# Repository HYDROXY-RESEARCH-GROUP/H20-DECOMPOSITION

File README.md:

# H20-DECOMPOSITION
H20 to HHO Genertor

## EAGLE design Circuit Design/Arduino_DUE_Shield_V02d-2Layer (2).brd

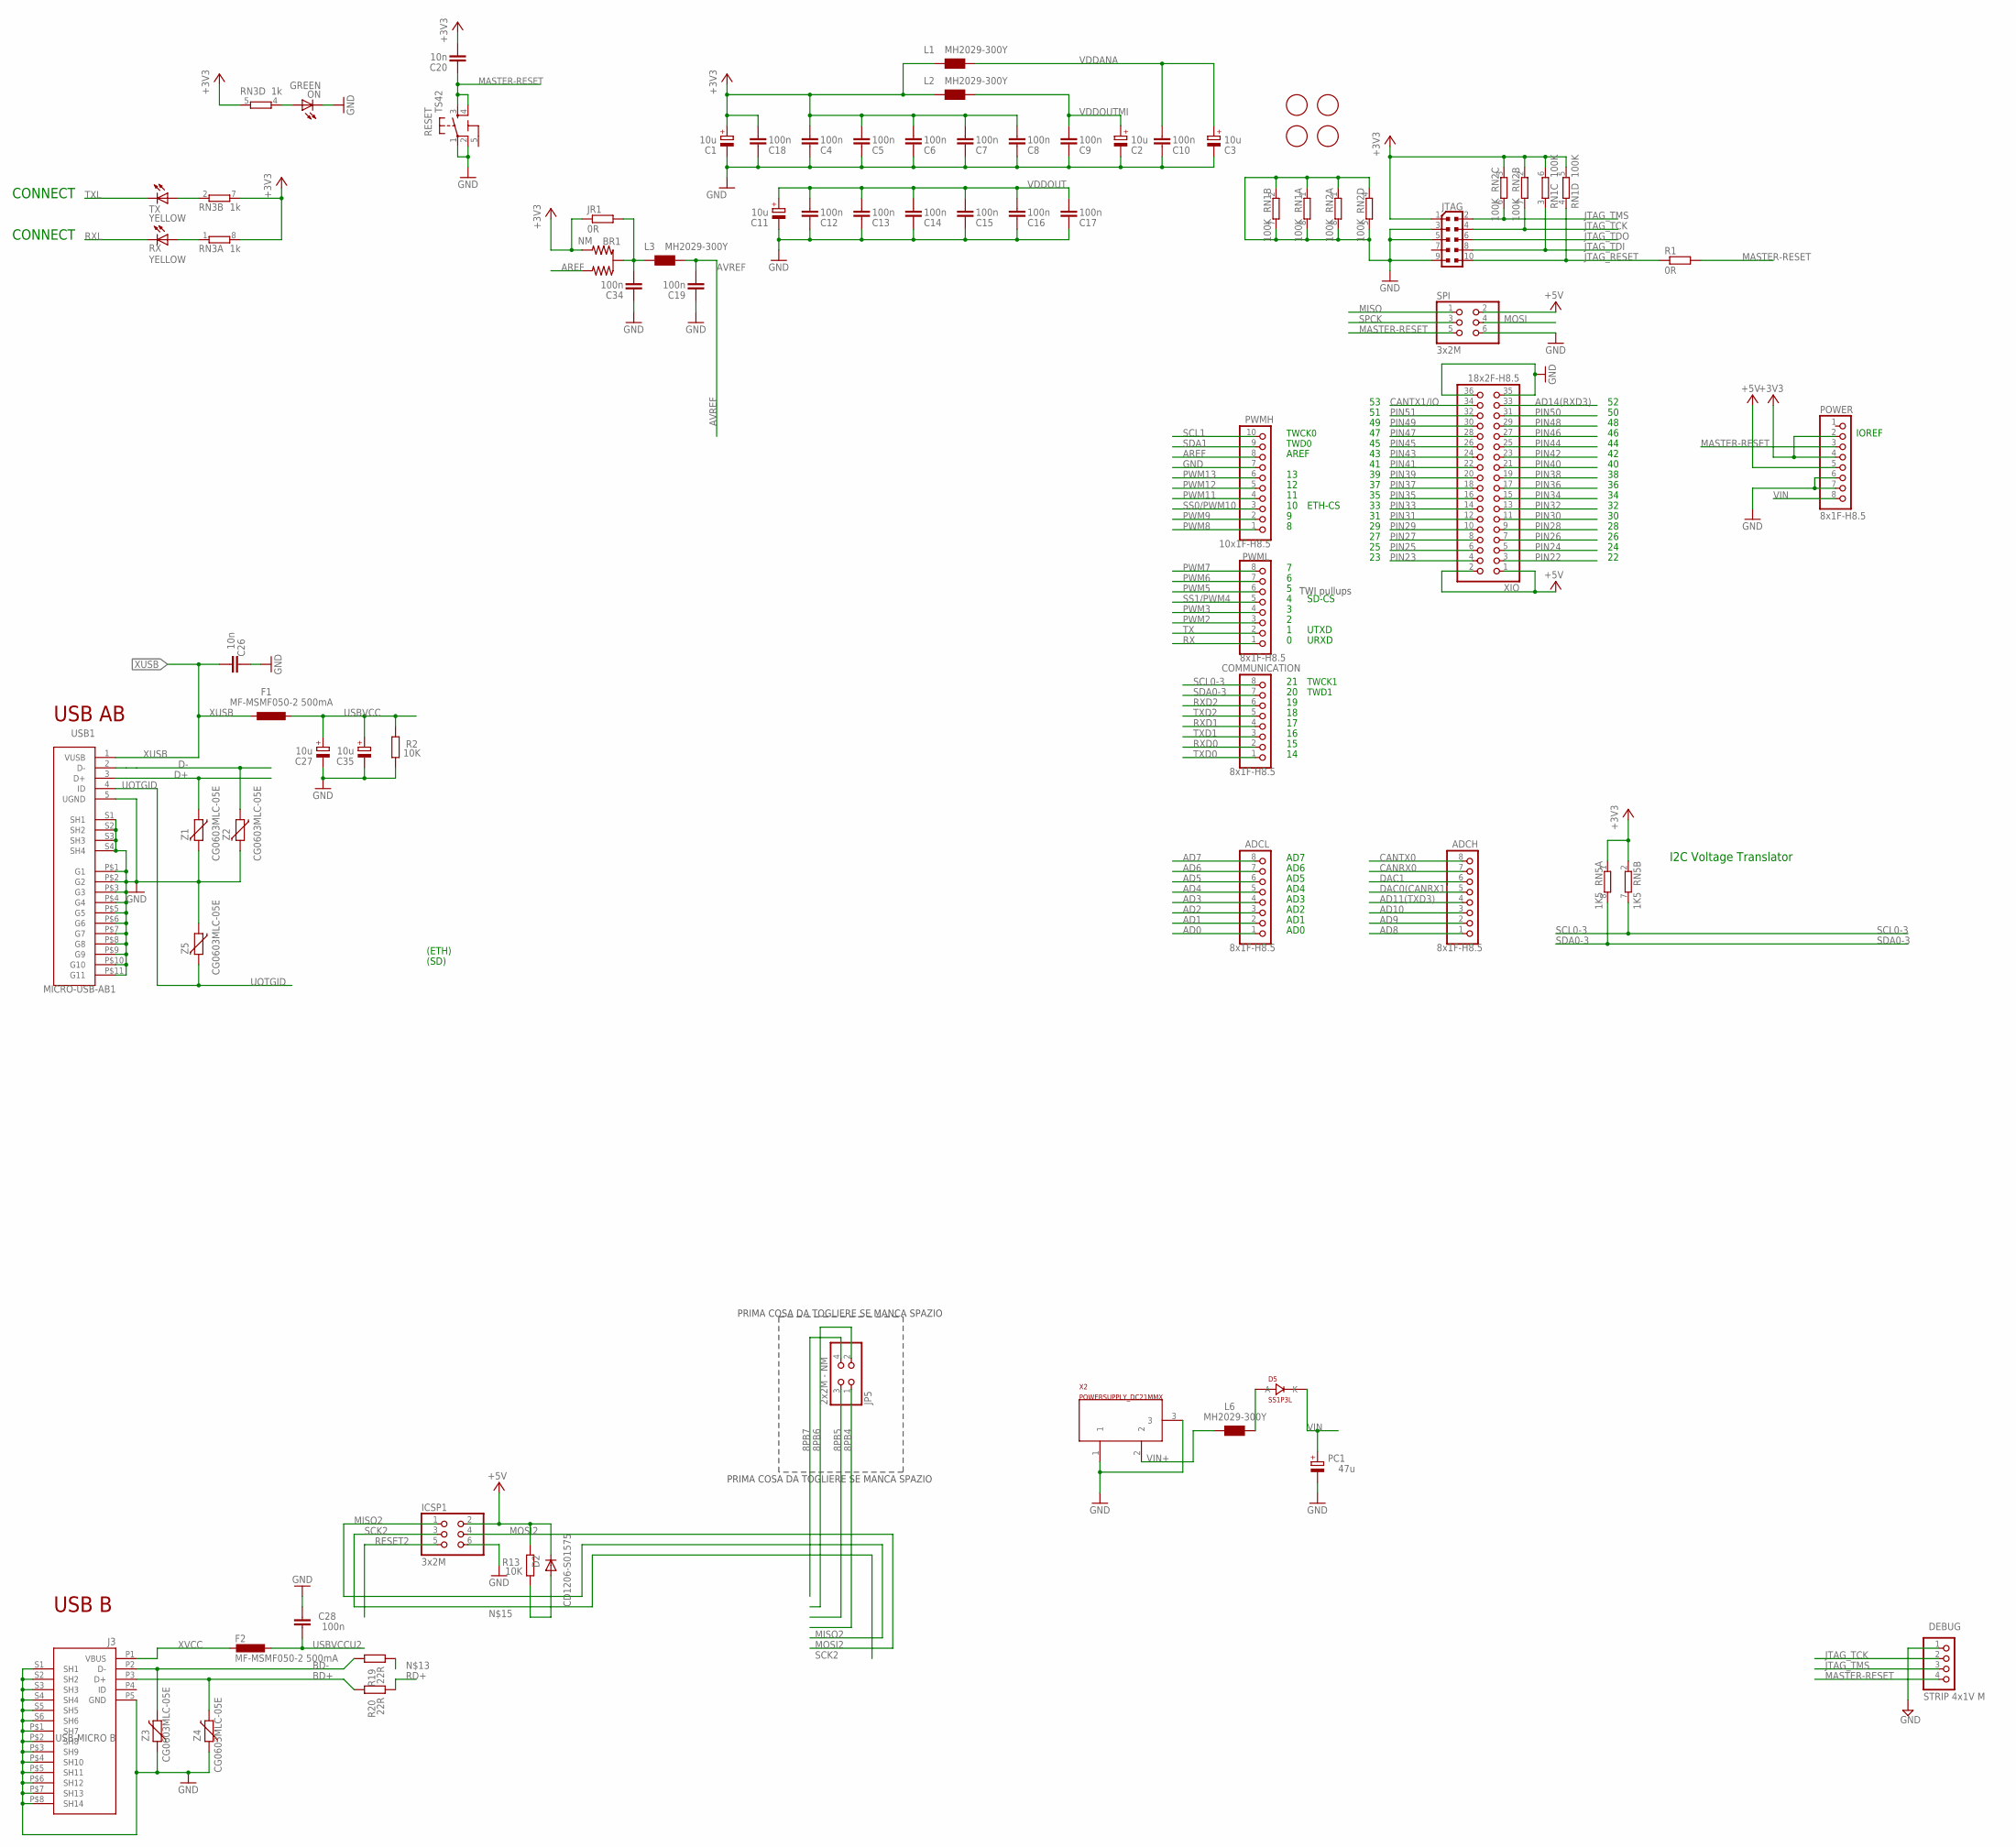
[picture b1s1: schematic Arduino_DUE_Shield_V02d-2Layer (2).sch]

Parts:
ADCH: 8x1F-H8.5; 1X08
ADCL: 8x1F-H8.5; 1X08
BR1: NM; J0402
C1, C2, C3, C11, C27, C35: 10u; SMC_B
C4, C5, C6, C7, C8, C9, C10, C12, C13, C14, C15, C16, C17, C18, C19, C28, C34: 100n; C0402
C20, C26: 10n; C0402
COMMUNICATION: 8x1F-H8.5; 1X08
D2: CD1206-S01575; MINIMELF
D5: SS1P3L; DO220AAL
DEBUG: STRIP 4x1V M; 1X04
F1, F2: MF-MSMF050-2 500mA; L1812
FID1, FID2, FID3, FID4: FIDUCIALMOUNT; FIDUCIA-MOUNT
ICSP1: 3x2M; 2X03
J3: USB-MICRO B; CON2_USB_MICRO_B_AT
JP5: 2x2M - NM; 2X02
JR1: 0R; R0402
JTAG: PINHEAD_PINHD-2X5PASSO127; PINHEAD_2X05_127
L1, L2, L3, L6: MH2029-300Y; 0805
ON: GREEN; CHIP-LED0805
PC1: 47u; PANASONIC_D
POWER: 8x1F-H8.5; 1X08
PWMH: 10x1F-H8.5; 1X10
PWML: 8x1F-H8.5; 1X08
R1: 0R; R0402
R2, R13: 10K; R0402
R19, R20: 22R; R0402
RESET: TS42
RN1, RN2: 100K; CAT16
RN3: 1k; CAY16
RN5: 1K5; CAT16
RX: YELLOW; CHIP-LED0805
SPI: 3x2M; 2X03
TX: YELLOW; CHIP-LED0805
USB1: MICRO-USB-AB1; MCR-AB1-S-RA-SMT
X2: POWERSUPPLY_DC21MMX; POWERSUPPLY_DC-21MM
XIO: 18x2F-H8.5; 2X18
Z1, Z2, Z3, Z4, Z5: CG0603MLC-05E; CT/CN0603

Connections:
5-GND: RESET.5 (5-GND)
8PB4: JP5.1
8PB5: JP5.3
8PB6: JP5.2
8PB7: JP5.4
+3V3: BR1.3 (2), C1.+, C4.2, C5.2, C6.2, C7.2, C8.2, C18.2, C20.2, JR1.1, JTAG.1, L1.1, L2.1, POWER.2, POWER.4, RN1.5 (2), RN1.6 (2), RN2.2 (1), RN2.3 (1), RN3.5 (2), RN3.7 (2), RN3.8 (2), RN5.1, RN5.2 (1)
+5V: D2.C, ICSP1.2, POWER.5, R13.2, SPI.2, XIO.1, XIO.2
AD0: ADCL.1
AD1: ADCL.2
AD2: ADCL.3
AD3: ADCL.4
AD4: ADCL.5
AD5: ADCL.6
AD6: ADCL.7
AD7: ADCL.8
AD8: ADCH.1
AD9: ADCH.2
AD10: ADCH.3
AD11(TXD3): ADCH.4
AD14(RXD3): XIO.33
AREF: BR1.1, PWMH.8
AVREF: C19.2, L3.2
AVREFL: BR1.2 (C), C34.2, JR1.2, L3.1
BD+: J3.P3 (D+), R20.2, Z4.2
BD-: J3.P2 (D-), R19.2, Z3.2
CANRX0: ADCH.7
CANTX0: ADCH.8
CANTX1/IO: XIO.34
D+: USB1.3 (D+), Z1.1
D-: USB1.2 (D-), Z2.1
DAC0(CANRX1): ADCH.5
DAC1: ADCH.6
GND: C1.-, C2.-, C3.-, C4.1, C5.1, C6.1, C7.1, C8.1, C9.1, C10.1, C11.-, C12.1, C13.1, C14.1, C15.1, C16.1, C17.1, C18.1, C19.1, C26.2, C27.-, C28.2, C34.1, C35.-, DEBUG.1, ICSP1.6, J3.P5 (GND), J3.P$1 (SH7), J3.P$2 (SH8), J3.P$3 (SH9), J3.P$4 (SH10), J3.P$5 (SH11), J3.P$6 (SH12), J3.P$7 (SH13), J3.P$8 (SH14), J3.S1 (SH1), J3.S2 (SH2), J3.S3 (SH3), J3.S4 (SH4), J3.S5 (SH5), J3.S6 (SH6), JTAG.3, JTAG.5, JTAG.9, ON.C, PC1.-, POWER.6, POWER.7, PWMH.7, R2.1, RESET.1, RESET.2, RN1.1, RN1.2 (1), RN1.7 (2), RN1.8 (2), RN2.1, RN2.4 (1), RN2.5 (2), RN2.8 (2), SPI.6, USB1.5 (UGND), USB1.P$1 (G1), USB1.P$2 (G2), USB1.P$3 (G3), USB1.P$4 (G4), USB1.P$5 (G5), USB1.P$6 (G6), USB1.P$7 (G7), USB1.P$8 (G8), USB1.P$9 (G9), USB1.P$10 (G10), USB1.P$11 (G11), USB1.S1 (SH1), USB1.S2 (SH2), USB1.S3 (SH3), USB1.S4 (SH4), X2.1, X2.3, XIO.35, XIO.36, Z1.2, Z2.2, Z3.1, Z4.1, Z5.1
JTAG_RESET: JTAG.10, R1.1, RN1.4 (1)
JTAG_TCK: DEBUG.2, JTAG.4, RN2.7 (2)
JTAG_TDI: JTAG.8, RN1.3 (1)
JTAG_TDO: JTAG.6
JTAG_TMS: DEBUG.3, JTAG.2, RN2.6 (2)
MASTER-RESET: C20.1, DEBUG.4, POWER.3, R1.2, RESET.3, RESET.4, SPI.5
MISO: SPI.1
MISO2: ICSP1.1
MOSI: SPI.4
MOSI2: ICSP1.4
unnamed: ON.A, RN3.4 (1)
unnamed: D5.P$2 (A), L6.1
unnamed: D2.A, R13.1
unnamed: RN3.1, RX.A
unnamed: RN3.2 (1), TX.A
PIN22: XIO.3
PIN23: XIO.4
PIN24: XIO.5
PIN25: XIO.6
PIN26: XIO.7
PIN27: XIO.8
PIN28: XIO.9
PIN29: XIO.10
PIN30: XIO.11
PIN31: XIO.12
PIN32: XIO.13
PIN33: XIO.14
PIN34: XIO.15
PIN35: XIO.16
PIN36: XIO.17
PIN37: XIO.18
PIN38: XIO.19
PIN39: XIO.20
PIN40: XIO.21
PIN41: XIO.22
PIN42: XIO.23
PIN43: XIO.24
PIN44: XIO.25
PIN45: XIO.26
PIN46: XIO.27
PIN47: XIO.28
PIN48: XIO.29
PIN49: XIO.30
PIN50: XIO.31
PIN51: XIO.32
PWM2: PWML.3
PWM3: PWML.4
PWM5: PWML.6
PWM6: PWML.7
PWM7: PWML.8
PWM8: PWMH.1
PWM9: PWMH.2
PWM11: PWMH.4
PWM12: PWMH.5
PWM13: PWMH.6
RD+: R20.1
RESET2: ICSP1.5
RX: PWML.1
RXD0: COMMUNICATION.2
RXD1: COMMUNICATION.4
RXD2: COMMUNICATION.6
RXL: RX.C
SCK2: ICSP1.3
SCL0-3: COMMUNICATION.8, RN5.7 (2)
SCL1: PWMH.10
SDA0-3: COMMUNICATION.7, RN5.8 (2)
SDA1: PWMH.9
SPCK: SPI.3
SS0/PWM10: PWMH.3
SS1/PWM4: PWML.5
TX: PWML.2
TXD0: COMMUNICATION.1
TXD1: COMMUNICATION.3
TXD2: COMMUNICATION.5
TXL: TX.C
UOTGID: USB1.4 (ID), Z5.2
USBVCC: C27.+, C35.+, F1.1, R2.2
USBVCCU2: C28.1, F2.1
VDDANA: C3.+, C10.2, L1.2
VDDOUT: C11.+, C12.2, C13.2, C14.2, C15.2, C16.2, C17.2
VDDOUTMI: C2.+, C9.2, L2.2
VIN: D5.P$1 (K), PC1.+, POWER.8
VIN+: L6.2, X2.2
XUSB: C26.1, F1.2, USB1.1 (VUSB)
XVCC: F2.2, J3.P1 (VBUS)

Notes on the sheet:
TWI pullups
TWCK1
TWD1
IOREF
TWCK0
TWD0
AD1
AD2
AD3
AD4
AD5
AD6
AD0
USB AB
AREF
AD7
SD-CS
CONNECT
UTXD
URXD
(ETH)
(SD)
ETH-CS
I2C Voltage Translator
PRIMA COSA DA TOGLIERE SE MANCA SPAZIO
USB B

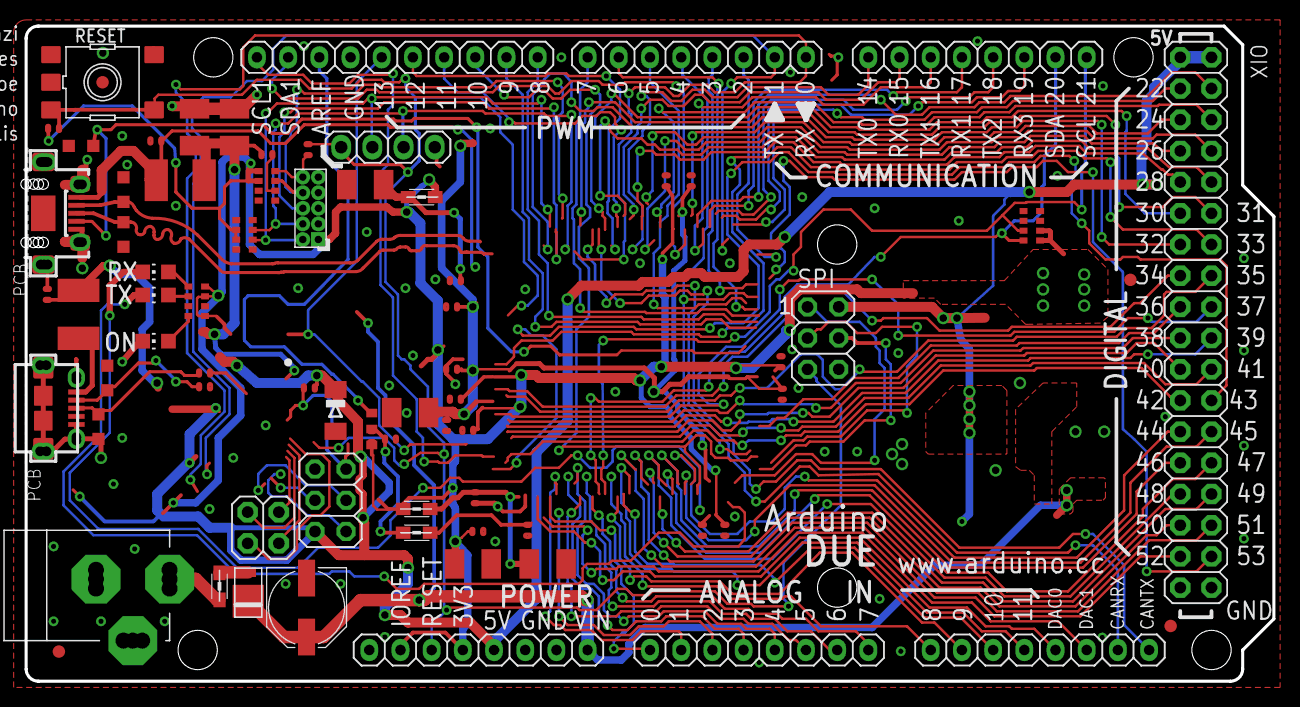
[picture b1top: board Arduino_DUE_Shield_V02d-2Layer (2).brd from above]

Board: 2 copper layers, 101.6 x 53.3 mm, 73 parts (0 on the bottom side), 32 nets.

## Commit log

2015-03-20 File Transfer
    Upload project files...
2015-03-20 R&D Files
    Uploading R&D Files resouces
2015-03-22 Create Class Files
2015-03-22 Display output layout
2015-03-22 Restructure Directories
    Re-organizes file structure
2015-03-24 Nightly Build 22/03/2015
2015-04-07 Weekly Build 07/APR/2015
    Separated functions into class based approach.
2016-11-20 Revisited (Nov 20, 2016)
    Optimizing Code.
2017-11-26 Backup_2017-Nov-25
    Regular Backup
2018-01-19 backup 2018-01-19
2020-12-29 Initial Migration to the PlatformIO IDE.
2020-12-30 Project reboot Dec 2020
2020-12-31 Dec-2020 Revisions
2020-12-31 RebasebBranch after migration to Platform IO
2020-12-31 PlatformIO Merges onto Dev branch
2021-01-10 multiple sources post merge point
2021-01-11 UIX Config file updates
